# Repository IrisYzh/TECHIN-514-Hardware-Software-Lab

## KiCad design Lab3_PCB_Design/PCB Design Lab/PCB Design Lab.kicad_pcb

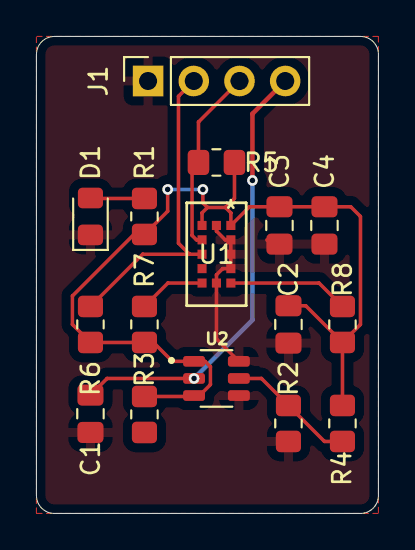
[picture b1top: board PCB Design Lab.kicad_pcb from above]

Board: 2 copper layers, 19.0 x 26.5 mm, 16 parts (0 on the bottom side), 9 nets.

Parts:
C1, C2: 0.47; C_0805_2012Metric_Pad1.18x1.45mm_HandSolder
C3: 100nF; C_0805_2012Metric_Pad1.18x1.45mm_HandSolder
C4: 4.7; C_0805_2012Metric_Pad1.18x1.45mm_HandSolder
D1: LED; LED_0805_2012Metric_Pad1.15x1.40mm_HandSolder
J1: Conn_01x04_Pin; PinSocket_1x04_P2.54mm_Vertical
R1: 1k; R_0805_2012Metric_Pad1.20x1.40mm_HandSolder
R2, R4, R5, R6, R7, R8: R; R_0805_2012Metric_Pad1.20x1.40mm_HandSolder
R3: 330k; R_0805_2012Metric_Pad1.20x1.40mm_HandSolder
U1: VL53L4CDV0DH/1; LGA12_STM
U2: ADP3331ARTZ-REEL7; SOT95P280X145-6N

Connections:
+2V8: C2.2, C3.1, C4.1, R1.1, R3.1, R3.2, R4.1, R5.1, R6.1, R7.1, R8.1, U1.1 (AVDDVCSEL), U1.11 (AVDD), U2.1 (OUT), U2.3 (~ERR)
+5V: C1.1, J1.4, U2.2 (IN)
/SCL: J1.3, R5.2, U1.10 (SCL)
/SDA: J1.2, R6.2, U1.9 (SDA)
GND: C1.2, C2.1, C3.2, C4.2, D1.1 (K), J1.1, R2.1, U1.2 (AVSSVCSEL), U1.3 (GND), U1.4 (GN2), U1.6 (GND3), U1.12 (GND4), U2.4 (GND), U2.6 (~SD)
unnamed: D1.2 (A), R1.2
unnamed: R7.2, U1.7 (GPIO1)
unnamed: R8.2, U1.5 (XSHUT)
unnamed: R2.2, R4.2, U2.5 (FB)

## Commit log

2026-01-15 Upload Lab2
2026-01-15 Remove Lab1_PlatformIO from repo
2026-01-15 Re-upload Lab1_PlatformIO
2026-01-28 update lab4
2026-01-30 update PCB lab
2026-01-30 update BOM
2026-02-04 Update Lab5
